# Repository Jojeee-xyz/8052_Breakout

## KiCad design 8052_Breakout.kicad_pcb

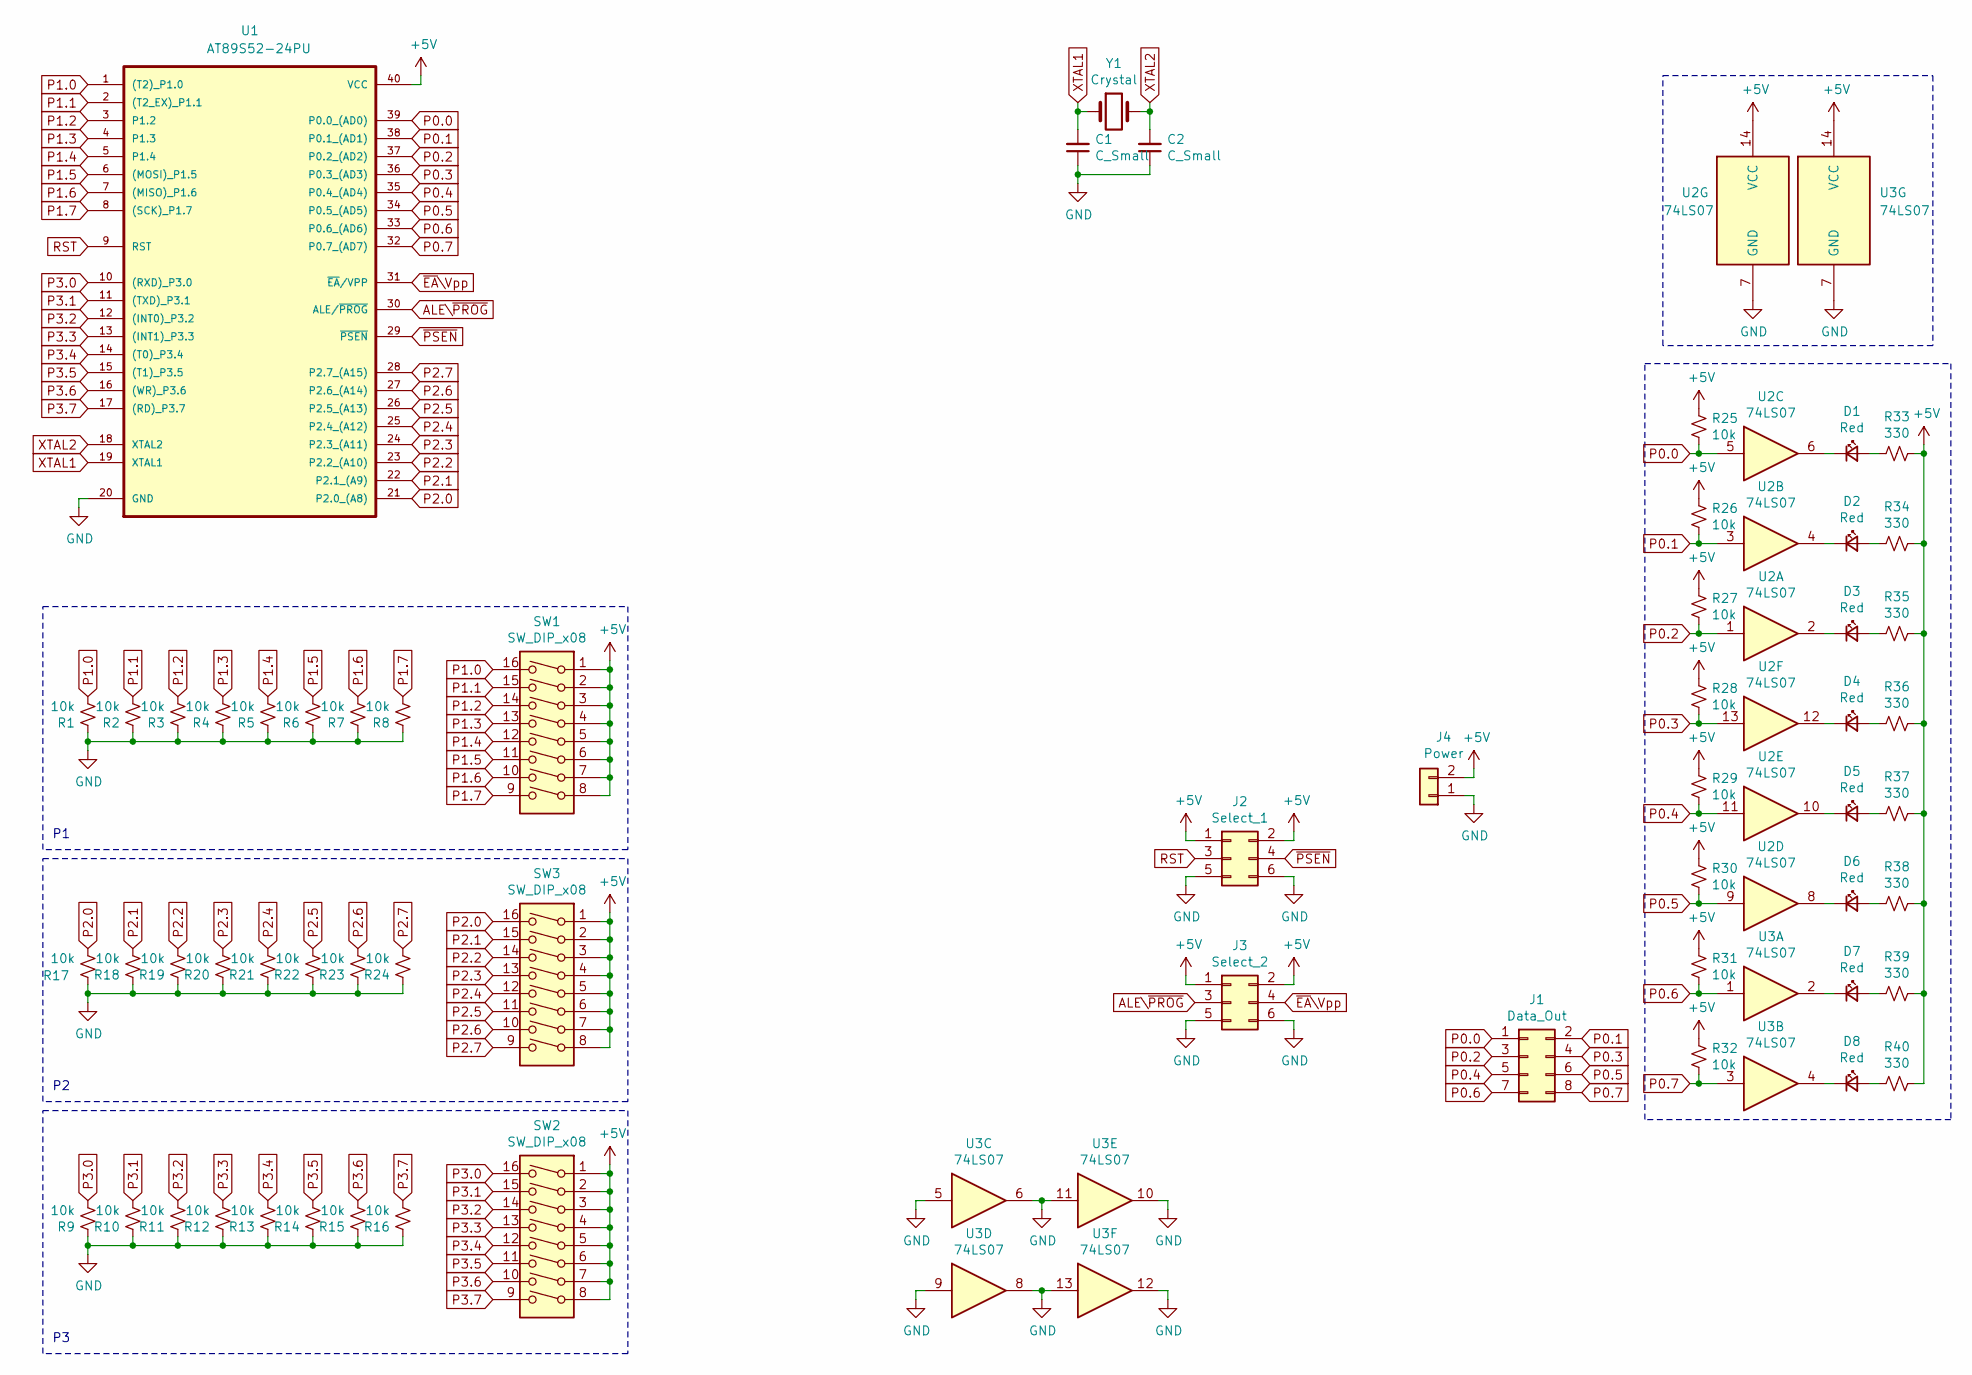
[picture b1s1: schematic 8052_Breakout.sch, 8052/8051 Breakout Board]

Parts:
C1, C2: C_Small; C_0805_2012Metric_Pad1.18x1.45mm_HandSolder
D1, D2, D3, D4, D5, D6, D7, D8: Red; LED_D3.0mm
J1: Data_Out; PinSocket_2x04_P2.54mm_Vertical
J2: Select_1; PinSocket_2x03_P2.54mm_Vertical
J3: Select_2; PinSocket_2x03_P2.54mm_Vertical
J4: Power; PinSocket_1x02_P2.54mm_Horizontal
R1, R2, R3, R4, R5, R6, R7, R8, R9, R10, R11, R12, R13, R14, R15, R16, R17, R18, R19, R20, R21, R22, R23, R24, R25, R26, R27, R28, R29, R30, R31, R32: 10k; R_0805_2012Metric_Pad1.20x1.40mm_HandSolder
R33, R34, R35, R36, R37, R38, R39, R40: 330; R_0805_2012Metric_Pad1.20x1.40mm_HandSolder
SW1, SW2, SW3: SW_DIP_x08; SW_DIP_SPSTx08_Slide_9.78x22.5mm_W7.62mm_P2.54mm
U1: AT89S52-24PU; DIP-40_W15.24mm_Socket_LongPads
U2, U3: 74LS07; DIP-14_W10.16mm_LongPads
Y1: Crystal; Crystal_HC49-4H_Vertical

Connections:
+5V: J2.1, J2.2, J3.1, J3.2, J4.2, R25.1, R26.1, R27.1, R28.1, R29.1, R30.1, R31.1, R32.1, R33.1, R34.1, R35.1, R36.1, R37.1, R38.1, R39.1, R40.1, SW1.1, SW1.2, SW1.3, SW1.4, SW1.5, SW1.6, SW1.7, SW1.8, SW2.1, SW2.2, SW2.3, SW2.4, SW2.5, SW2.6, SW2.7, SW2.8, SW3.1, SW3.2, SW3.3, SW3.4, SW3.5, SW3.6, SW3.7, SW3.8, U1.40 (VCC), U2.14 (VCC), U3.14 (VCC)
ALE\~PROG~: J3.3, U1.30 (ALE/~PROG)
GND: C1.1, C2.1, J2.5, J2.6, J3.5, J3.6, J4.1, R1.1, R2.1, R3.1, R4.1, R5.1, R6.1, R7.1, R8.1, R9.1, R10.1, R11.1, R12.1, R13.1, R14.1, R15.1, R16.1, R17.1, R18.1, R19.1, R20.1, R21.1, R22.1, R23.1, R24.1, U1.20 (GND), U2.7 (GND), U3.5, U3.6, U3.7 (GND), U3.8, U3.9, U3.10, U3.11, U3.12, U3.13
unnamed: D1.1 (K), U2.6
unnamed: D1.2 (A), R33.2
unnamed: D2.1 (K), U2.4
unnamed: D2.2 (A), R34.2
unnamed: D3.1 (K), U2.2
unnamed: D3.2 (A), R35.2
unnamed: D4.1 (K), U2.12
unnamed: D4.2 (A), R36.2
unnamed: D5.1 (K), U2.10
unnamed: D5.2 (A), R37.2
unnamed: D6.1 (K), U2.8
unnamed: D6.2 (A), R38.2
unnamed: D7.1 (K), U3.2
unnamed: D7.2 (A), R39.2
unnamed: D8.1 (K), U3.4
unnamed: D8.2 (A), R40.2
P0.0: J1.1, R25.2, U1.39 (P0.0_(AD0)), U2.5
P0.1: J1.2, R26.2, U1.38 (P0.1_(AD1)), U2.3
P0.2: J1.3, R27.2, U1.37 (P0.2_(AD2)), U2.1
P0.3: J1.4, R28.2, U1.36 (P0.3_(AD3)), U2.13
P0.4: J1.5, R29.2, U1.35 (P0.4_(AD4)), U2.11
P0.5: J1.6, R30.2, U1.34 (P0.5_(AD5)), U2.9
P0.6: J1.7, R31.2, U1.33 (P0.6_(AD6)), U3.1
P0.7: J1.8, R32.2, U1.32 (P0.7_(AD7)), U3.3
P1.0: R1.2, SW1.16, U1.1 ((T2)_P1.0)
P1.1: R2.2, SW1.15, U1.2 ((T2_EX)_P1.1)
P1.2: R3.2, SW1.14, U1.3 (P1.2)
P1.3: R4.2, SW1.13, U1.4 (P1.3)
P1.4: R5.2, SW1.12, U1.5 (P1.4)
P1.5: R6.2, SW1.11, U1.6 ((MOSI)_P1.5)
P1.6: R7.2, SW1.10, U1.7 ((MISO)_P1.6)
P1.7: R8.2, SW1.9, U1.8 ((SCK)_P1.7)
P2.0: R17.2, SW3.16, U1.21 (P2.0_(A8))
P2.1: R18.2, SW3.15, U1.22 (P2.1_(A9))
P2.2: R19.2, SW3.14, U1.23 (P2.2_(A10))
P2.3: R20.2, SW3.13, U1.24 (P2.3_(A11))
P2.4: R21.2, SW3.12, U1.25 (P2.4_(A12))
P2.5: R22.2, SW3.11, U1.26 (P2.5_(A13))
P2.6: R23.2, SW3.10, U1.27 (P2.6_(A14))
P2.7: R24.2, SW3.9, U1.28 (P2.7_(A15))
P3.0: R9.2, SW2.16, U1.10 ((RXD)_P3.0)
P3.1: R10.2, SW2.15, U1.11 ((TXD)_P3.1)
P3.2: R11.2, SW2.14, U1.12 ((INT0)_P3.2)
P3.3: R12.2, SW2.13, U1.13 ((INT1)_P3.3)
P3.4: R13.2, SW2.12, U1.14 ((T0)_P3.4)
P3.5: R14.2, SW2.11, U1.15 ((T1)_P3.5)
P3.6: R15.2, SW2.10, U1.16 ((WR)_P3.6)
P3.7: R16.2, SW2.9, U1.17 ((RD)_P3.7)
RST: J2.3, U1.9 (RST)
XTAL1: C1.2, U1.19 (XTAL1), Y1.1
XTAL2: C2.2, U1.18 (XTAL2), Y1.2
~EA~\Vpp: J3.4, U1.31 (~EA~/VPP)
~PSEN~: J2.4, U1.29 (~PSEN)

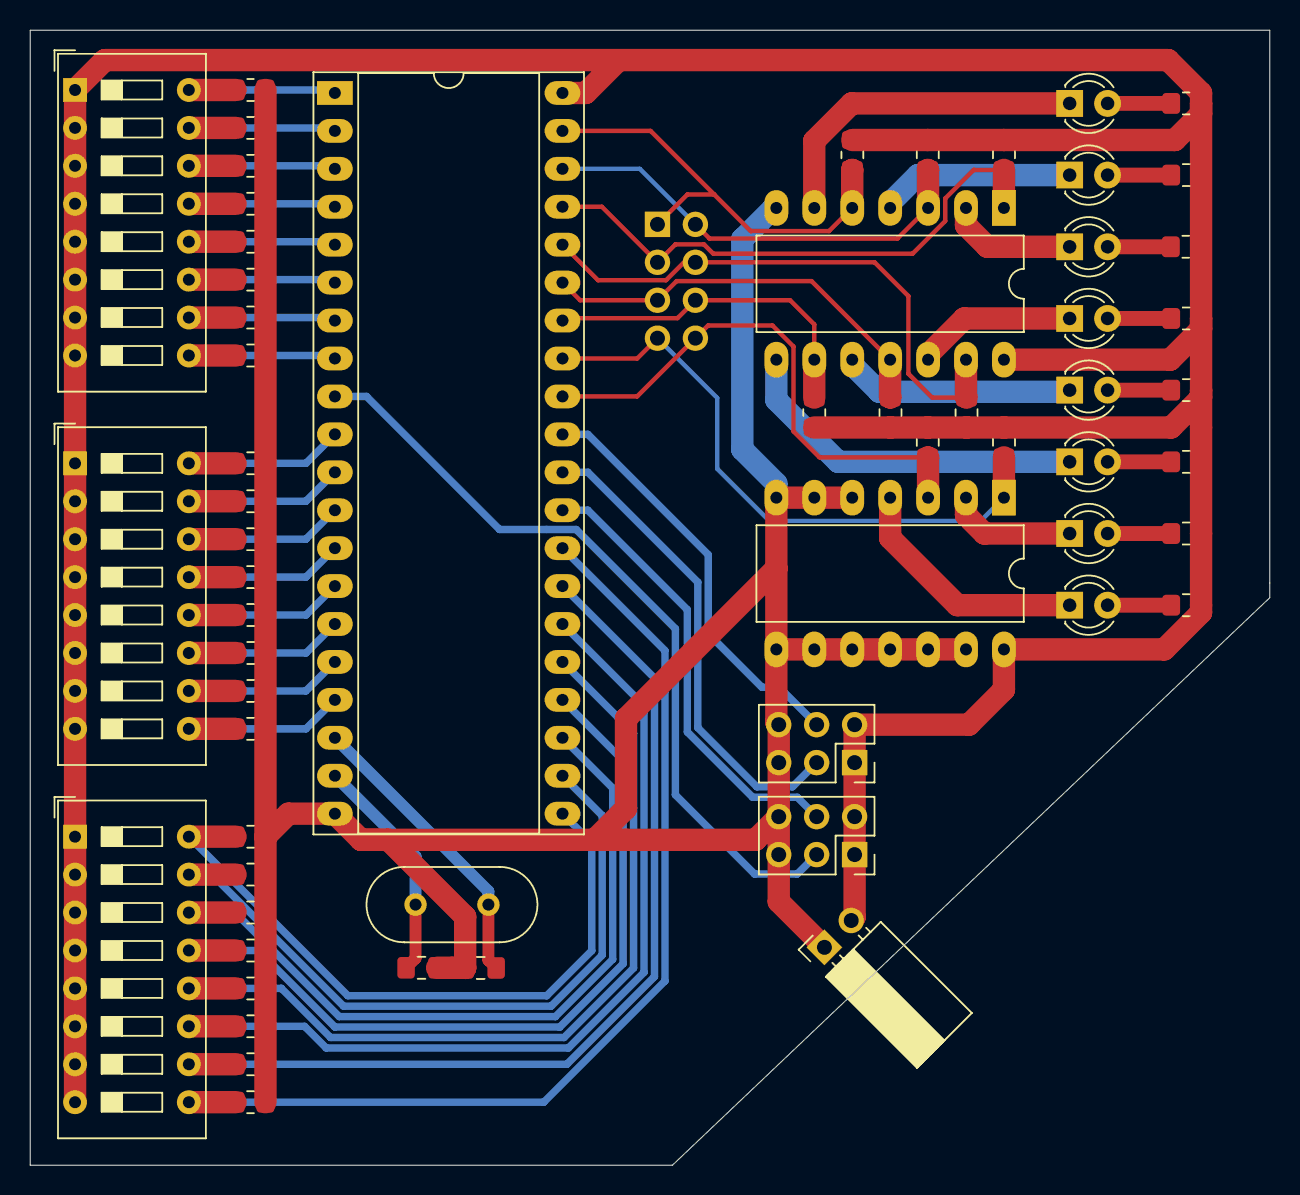
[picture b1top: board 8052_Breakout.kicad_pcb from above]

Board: 2 copper layers, 83.0 x 76.0 mm, 61 parts (1 on the bottom side), 56 nets.

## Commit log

2021-12-02 Inital commit
